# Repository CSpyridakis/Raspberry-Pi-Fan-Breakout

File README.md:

# Raspberry-Pi-Fan-Breakout

Compact and lightweight Raspberry Pi breakout board design with fan onboard.

### Breakout 3D model

### Assembled top view

### Breakout on top of Raspberry Pi 4 with IMU sensor attached

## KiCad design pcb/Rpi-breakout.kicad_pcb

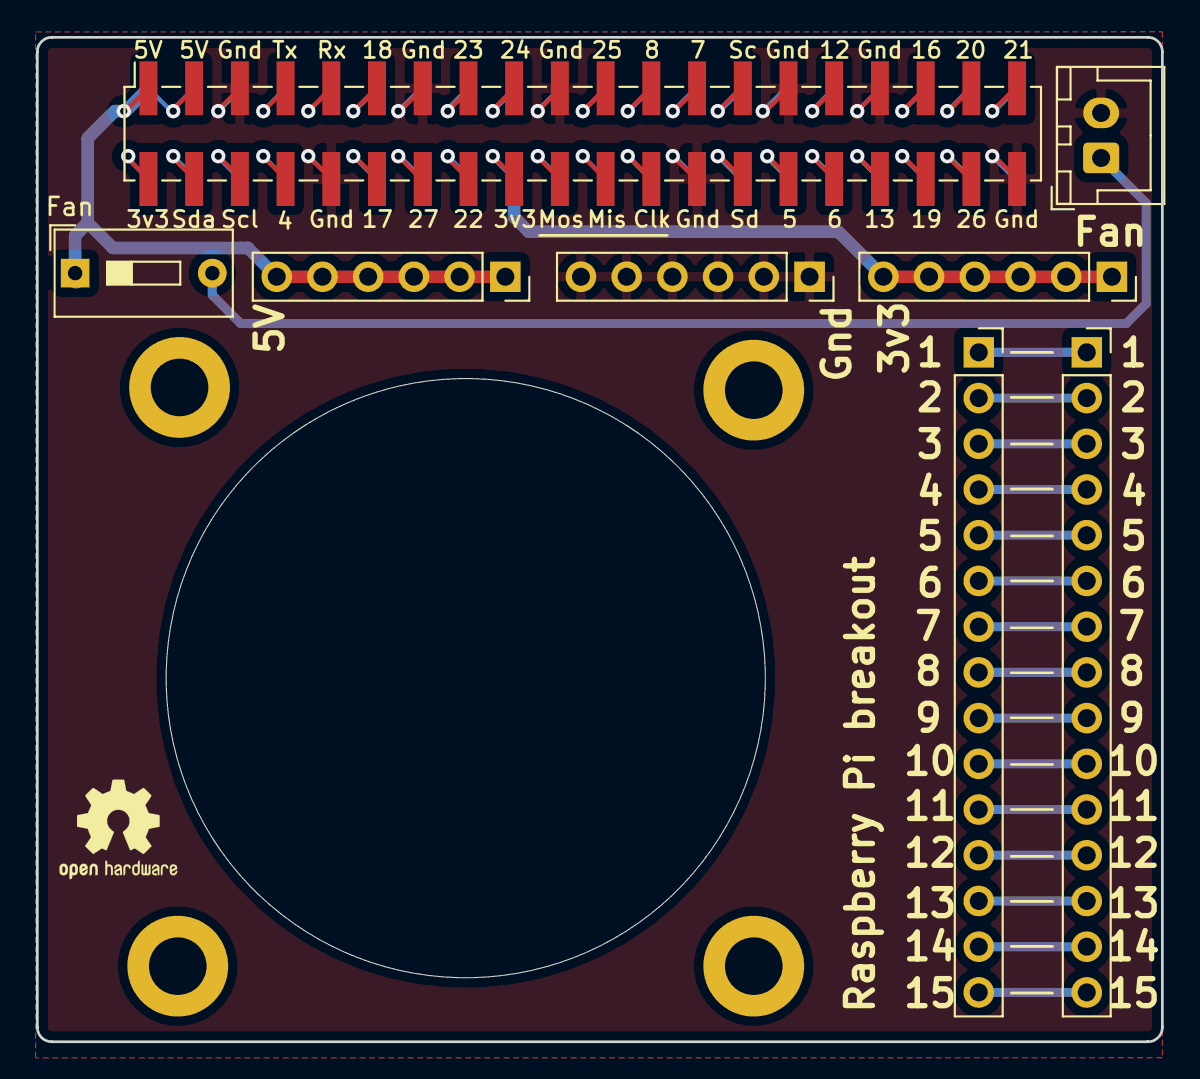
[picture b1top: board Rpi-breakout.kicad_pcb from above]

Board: 2 copper layers, 62.5 x 55.8 mm, 9 parts (1 on the bottom side), 48 nets.

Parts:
Fan: SW_SPST; SW_DIP_SPSTx01_Slide_9.78x4.72mm_W7.62mm_P2.54mm
J101: Upper Connector; PinSocket_2x20_P2.54mm_Vertical_SMD
J102: Fan; JST_XH_B2B-XH-A_1x02_P2.50mm_Vertical
J103, J104, J106: Conn_01x06_Female; PinSocket_1x06_P2.54mm_Vertical
J105: Rpi Connector; PinSocket_2x20_P2.54mm_Vertical_SMD
J107, J108: Conn_01x11_Female; PinSocket_1x15_P2.54mm_Vertical

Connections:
+3V3: J101.18, J104.1, J104.2, J104.3, J104.4, J104.5, J104.6, J105.17
+5V: Fan.1, J101.1, J101.3, J105.2, J105.4, J106.1, J106.2, J106.3, J106.4, J106.5, J106.6
/C2: J101.2, J105.1
/C4: J101.4, J105.3
/C6: J101.6, J105.5
/C7: J101.7, J105.8
/C8: J101.8, J105.7
/C9: J101.9, J105.10
/C11: J101.11, J105.12
/C12: J101.12, J105.11
/C14: J101.14, J105.13
/C15: J101.15, J105.16
/C16: J101.16, J105.15
/C17: J101.17, J105.18
/C20: J101.20, J105.19
/C21: J101.21, J105.22
/C22: J101.22, J105.21
/C23: J101.23, J105.24
/C24: J101.24, J105.23
/C25: J101.25, J105.26
/C27: J101.27, J105.28
/C28: J101.28, J105.27
/C30: J101.30, J105.29
/C31: J101.31, J105.32
/C32: J101.32, J105.31
/C34: J101.34, J105.33
/C35: J101.35, J105.36
/C36: J101.36, J105.35
/C37: J101.37, J105.38
/C38: J101.38, J105.37
/C39: J101.39, J105.40
GND: J101.5, J101.10, J101.13, J101.19, J101.26, J101.29, J101.33, J101.40, J102.2, J103.1, J103.2, J103.3, J103.4, J103.5, J103.6, J105.6, J105.9, J105.14, J105.20, J105.25, J105.30, J105.34, J105.39
unnamed: Fan.2, J102.1
unnamed: J107.1, J108.1
unnamed: J107.2, J108.2
unnamed: J107.3, J108.3
unnamed: J107.4, J108.4
unnamed: J107.5, J108.5
unnamed: J107.6, J108.6
unnamed: J107.7, J108.7
unnamed: J107.8, J108.8
unnamed: J107.9, J108.9
unnamed: J107.10, J108.10
unnamed: J107.11, J108.11
unnamed: J107.12, J108.12
unnamed: J107.13, J108.13
unnamed: J107.14, J108.14
unnamed: J107.15, J108.15

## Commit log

2021-07-10 Init
2021-08-02 Photos added

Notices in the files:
README.md:
MIT license
pcb/Rpi-breakout.kicad_pcb:
Copyright © 2021 Spyridakis Christos
